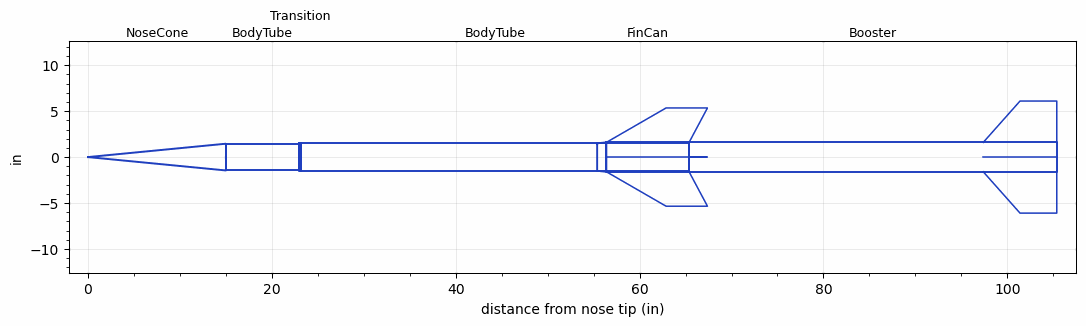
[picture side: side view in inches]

<RASAeroDocument>
 <FileVersion>2</FileVersion>
 <RocketDesign>
  <NoseCone>
   <Length>15</Length>
   <Diameter>2.91</Diameter>
   <Shape>Conical</Shape>
   <BluntRadius>0.065</BluntRadius>
   <Location>0</Location>
  </NoseCone>
  <BodyTube>
   <Length>7.94</Length>
   <Diameter>2.91</Diameter>
   <Location>15</Location>
   <Protuberance>
    <StreamlinedNoBaseDrag>0</StreamlinedNoBaseDrag>
    <StreamlinedWithBaseDrag>0.65</StreamlinedWithBaseDrag>
    <InclinedPlate1Angle>0</InclinedPlate1Angle>
    <InclinedPlate1FrontalArea>0</InclinedPlate1FrontalArea>
    <InclinedPlate2Angle>0</InclinedPlate2Angle>
    <InclinedPlate2FrontalArea>0</InclinedPlate2FrontalArea>
   </Protuberance>
  </BodyTube>
  <Transition>
   <Length>0.25</Length>
   <Diameter>3</Diameter>
   <Location>22.94</Location>
   <RearDiameter>3</RearDiameter>
  </Transition>
  <BodyTube>
   <Length>42.195</Length>
   <Diameter>3</Diameter>
   <Location>23.19</Location>
  </BodyTube>
  <FinCan>
   <Length>9</Length>
   <Diameter>3.19</Diameter>
   <InsideDiameter>3</InsideDiameter>
   <Location>65.385</Location>
   <ShoulderLength>1</ShoulderLength>
   <Offset>-9</Offset>
   <Fin>
    <Count>4</Count>
    <Chord>9</Chord>
    <Span>3.75</Span>
    <SweepDistance>6.5</SweepDistance>
    <TipChord>4.5</TipChord>
    <Thickness>0.15</Thickness>
    <LERadius>0.01</LERadius>
    <Location>9</Location>
    <AirfoilSection>Hexagonal</AirfoilSection>
    <FX1>0.512</FX1>
    <FX3>0.512</FX3>
   </Fin>
  </FinCan>
  <Booster>
   <Length>40</Length>
   <Diameter>3.19</Diameter>
   <InsideDiameter>3.19</InsideDiameter>
   <LaunchShoeArea>0.3</LaunchShoeArea>
   <Location>65.385</Location>
   <ShoulderLength>0</ShoulderLength>
   <Fin>
    <Count>4</Count>
    <Chord>8</Chord>
    <Span>4.5</Span>
    <SweepDistance>4</SweepDistance>
    <TipChord>4</TipChord>
    <Thickness>0.125</Thickness>
    <LERadius>0.01</LERadius>
    <Location>8</Location>
    <AirfoilSection>Hexagonal</AirfoilSection>
    <FX1>0.36</FX1>
    <FX3>0.36</FX3>
   </Fin>
  </Booster>
  <Surface>Camouflage Paint</Surface>
  <ModifiedBarrowman>True</ModifiedBarrowman>
  <Turbulence>True</Turbulence>
  <UseBooster1>False</UseBooster1>
  <UseBooster2>False</UseBooster2>
 </RocketDesign>
 <LaunchSite>
  <Altitude>2000</Altitude>
  <Pressure>0</Pressure>
  <RodAngle>1</RodAngle>
  <RodLength>20</RodLength>
  <Temperature>80</Temperature>
  <WindSpeed>5</WindSpeed>
 </LaunchSite>
 <Recovery>
  <Altitude1>1000</Altitude1>
  <Altitude2>2000</Altitude2>
  <DeviceType1>Parachute</DeviceType1>
  <DeviceType2>Parachute</DeviceType2>
  <Event1>True</Event1>
  <Event2>True</Event2>
  <Size1>9</Size1>
  <Size2>36</Size2>
  <EventType1>Apogee</EventType1>
  <EventType2>Altitude</EventType2>
  <CD1>0.8</CD1>
  <CD2>2</CD2>
 </Recovery>
 <SimulationList>
  <Simulation>
   <SustainerEngine>N3051  (TsKrush)</SustainerEngine>
   <SustainerLaunchWt>22.67</SustainerLaunchWt>
   <SustainerNozzleDiameter>2.5</SustainerNozzleDiameter>
   <SustainerCG>43</SustainerCG>
   <SustainerIgnitionDelay>6</SustainerIgnitionDelay>
   <Booster1Engine>M3140  (TsKrush)</Booster1Engine>
   <Booster1LaunchWt>38.84</Booster1LaunchWt>
   <Booster1SeparationDelay>0</Booster1SeparationDelay>
   <Booster1IgnitionDelay>0</Booster1IgnitionDelay>
   <Booster1CG>58.5</Booster1CG>
   <Booster1NozzleDiameter>2.75</Booster1NozzleDiameter>
   <IncludeBooster1>True</IncludeBooster1>
   <Booster2Delay>0</Booster2Delay>
   <IncludeBooster2>False</IncludeBooster2>
   <TimetoApogee>80.49825</TimetoApogee>
   <MaxAltitude>108559.2</MaxAltitude>
   <MaxVelocity>4589.513</MaxVelocity>
  </Simulation>
 </SimulationList>
</RASAeroDocument>
